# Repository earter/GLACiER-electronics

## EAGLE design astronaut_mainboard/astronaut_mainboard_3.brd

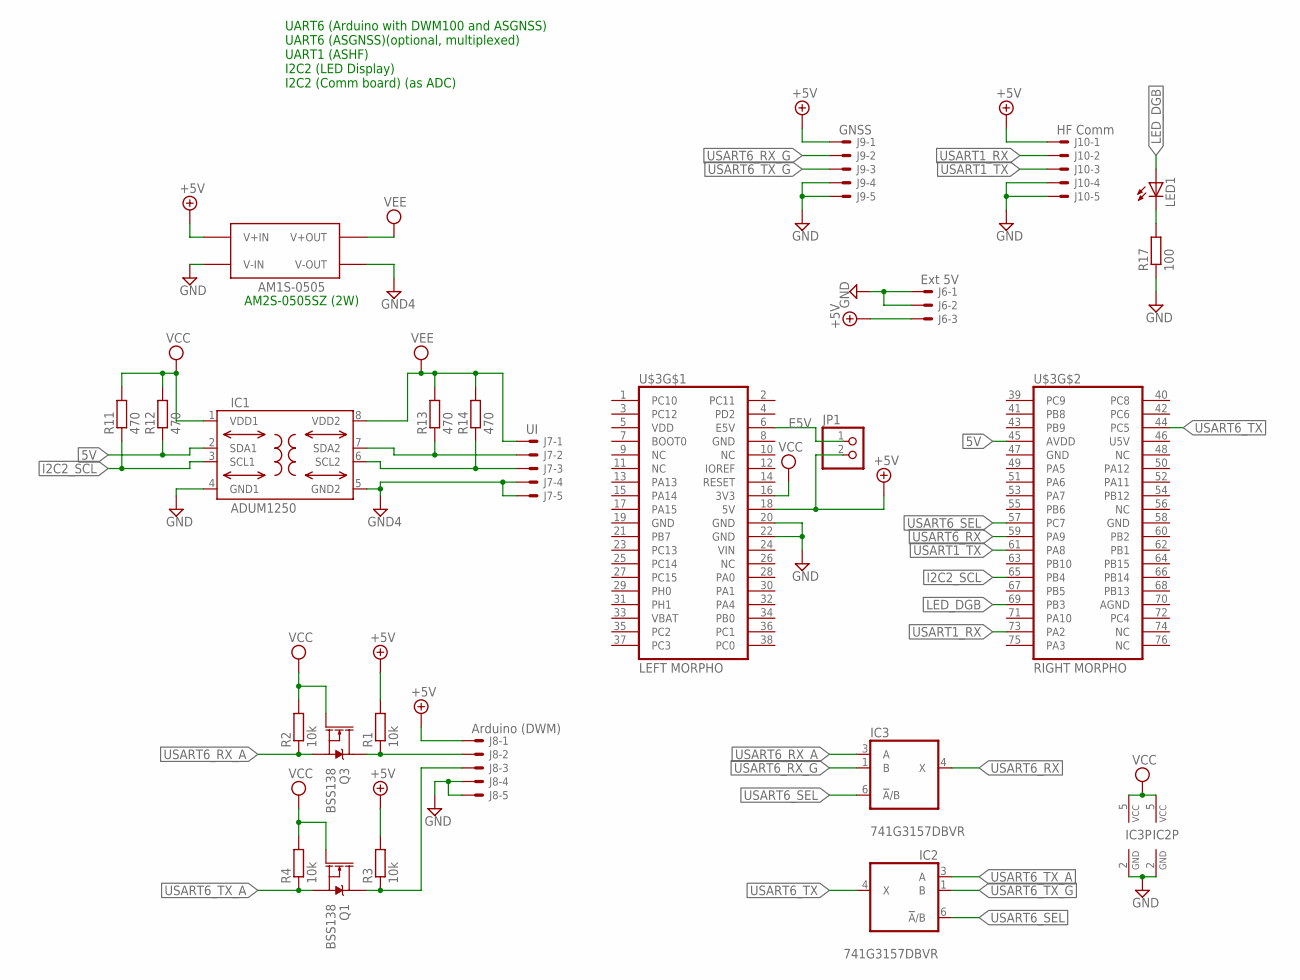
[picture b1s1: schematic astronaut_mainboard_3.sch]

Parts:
IC1: ADUM1250; SO8-COOL
IC2, IC3: 741G3157DBVR; DBV_R-PDSO-G6
J6: Ext 5V; 7395-03
J7: UI; 7395-05
J8: Arduino (DWM); 7395-05
J9: GNSS; 7395-05
J10: HF Comm; 7395-05
JP1: PINHD-1X2; 1X02
LED1: LEDSML1206; SML1206
Q1, Q3: BSS138; SOT23-3
R1, R2, R3, R4: 10k; R0805
R11, R12, R13, R14: 470; R0805
R17: 100; R0805
U$2: AM1S-0505; SIP4
U$3: NUCLEO_F411RE_MORPHO; MORPHO_HEADERS

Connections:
5V: IC1.2 (SDA1), R12.1, U$3.45 (AVDD)
+5V: J6.3, J8.1, J9.1, J10.1, JP1.2, R1.2, R3.2, U$2.P$2 (V+IN), U$3.18 (5V)
AGND: U$3.70 (AGND)
ARDU_RX: J8.2, Q3.3 (D), R1.1
ARDU_TX: J8.3, Q1.3 (D), R3.1
E5V: JP1.1, U$3.6 (E5V)
GND: IC1.4 (GND1), IC2.2 (GND), IC3.2 (GND), J6.1, J6.2, J8.4, J8.5, J9.4, J9.5, J10.4, J10.5, R17.1, U$2.P$1 (V-IN), U$3.8 (GND), U$3.19 (GND), U$3.20 (GND), U$3.22 (GND), U$3.47 (GND), U$3.58 (GND)
GND4: IC1.5 (GND2), J7.4, J7.5, U$2.P$3 (V-OUT)
I2C2_SCL: IC1.3 (SCL1), R11.1, U$3.65 (PB4)
LED_DGB: LED1.A, U$3.69 (PB3)
unnamed: LED1.C, R17.2
U5V: U$3.46 (U5V)
UI_SCL: IC1.6 (SCL2), J7.3, R14.1
UI_SDA: IC1.7 (SDA2), J7.2, R13.1
USART1_RX: J10.2, U$3.73 (PA2)
USART1_TX: J10.3, U$3.61 (PA8)
USART6_RX: IC3.4 (X), U$3.59 (PA9)
USART6_RX_A: IC3.3 (A), Q3.2 (S), R2.1
USART6_RX_G: IC3.1 (B), J9.2
USART6_SEL: IC2.6 (!A!/B), IC3.6 (!A!/B), U$3.57 (PC7)
USART6_TX: IC2.4 (X), U$3.44 (PC5)
USART6_TX_A: IC2.3 (A), Q1.2 (S), R4.1
USART6_TX_G: IC2.1 (B), J9.3
VBAT: U$3.33 (VBAT)
VCC: IC1.1 (VDD1), IC2.5 (VCC), IC3.5 (VCC), Q1.1 (G), Q3.1 (G), R2.2, R4.2, R11.2, R12.2, U$3.16 (3V3)
VDD: U$3.5 (VDD)
VEE: IC1.8 (VDD2), J7.1, R13.2, R14.2, U$2.P$4 (V+OUT)
VIN: U$3.24 (VIN)

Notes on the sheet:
UART6 (Arduino with DWM100 and ASGNSS) UART6 (ASGNSS)(optional, multiplexed) UART1 (ASHF) I2C2 (LED Display) I2C2 (Comm board) (as ADC)
AM2S-0505SZ (2W)

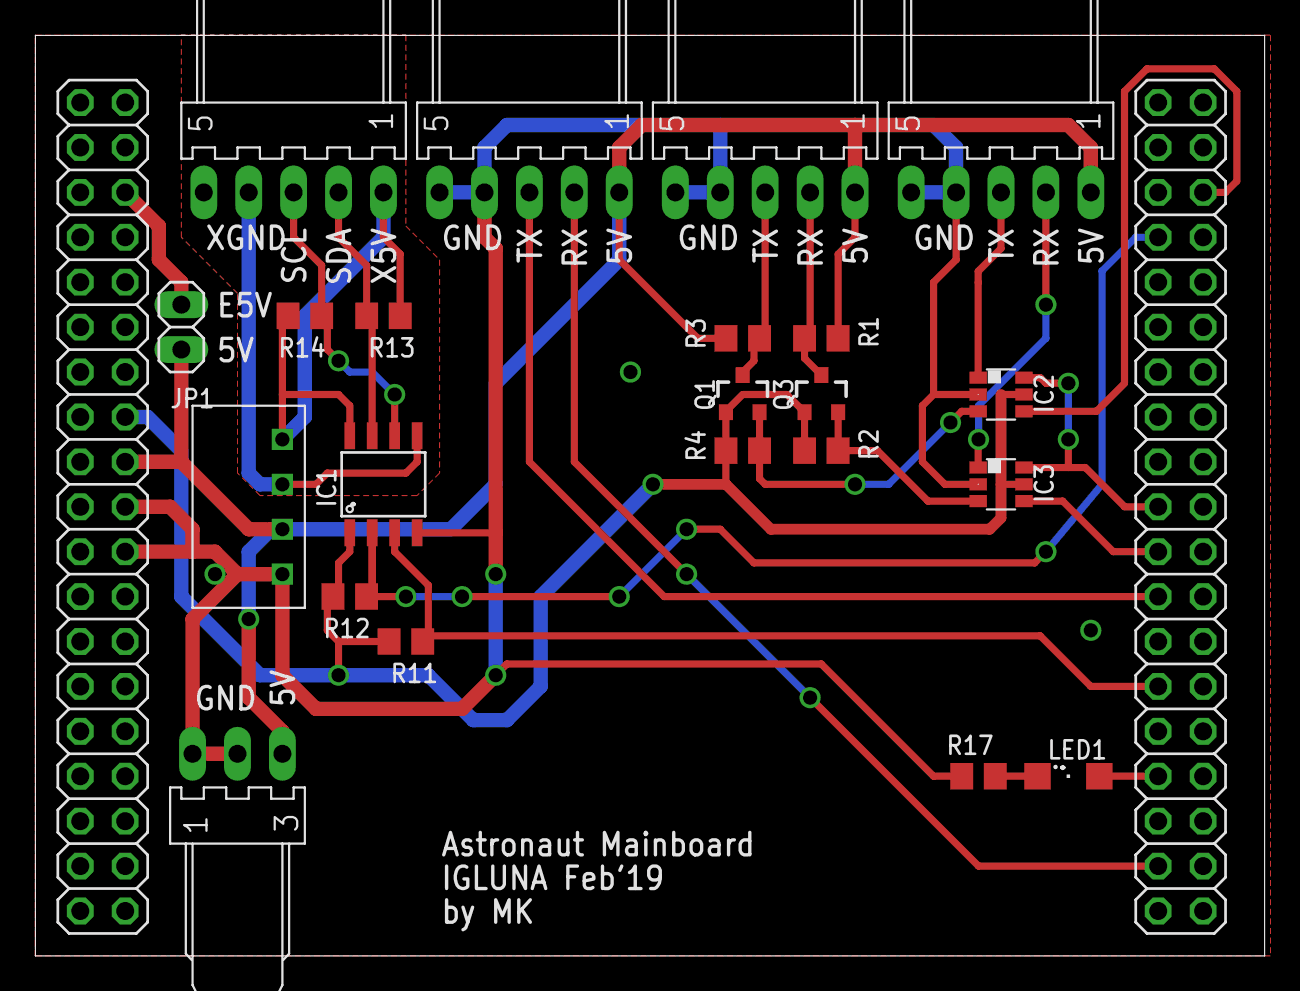
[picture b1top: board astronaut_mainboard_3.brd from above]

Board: 2 copper layers, 69.5 x 52.1 mm, 23 parts (0 on the bottom side), 23 nets.

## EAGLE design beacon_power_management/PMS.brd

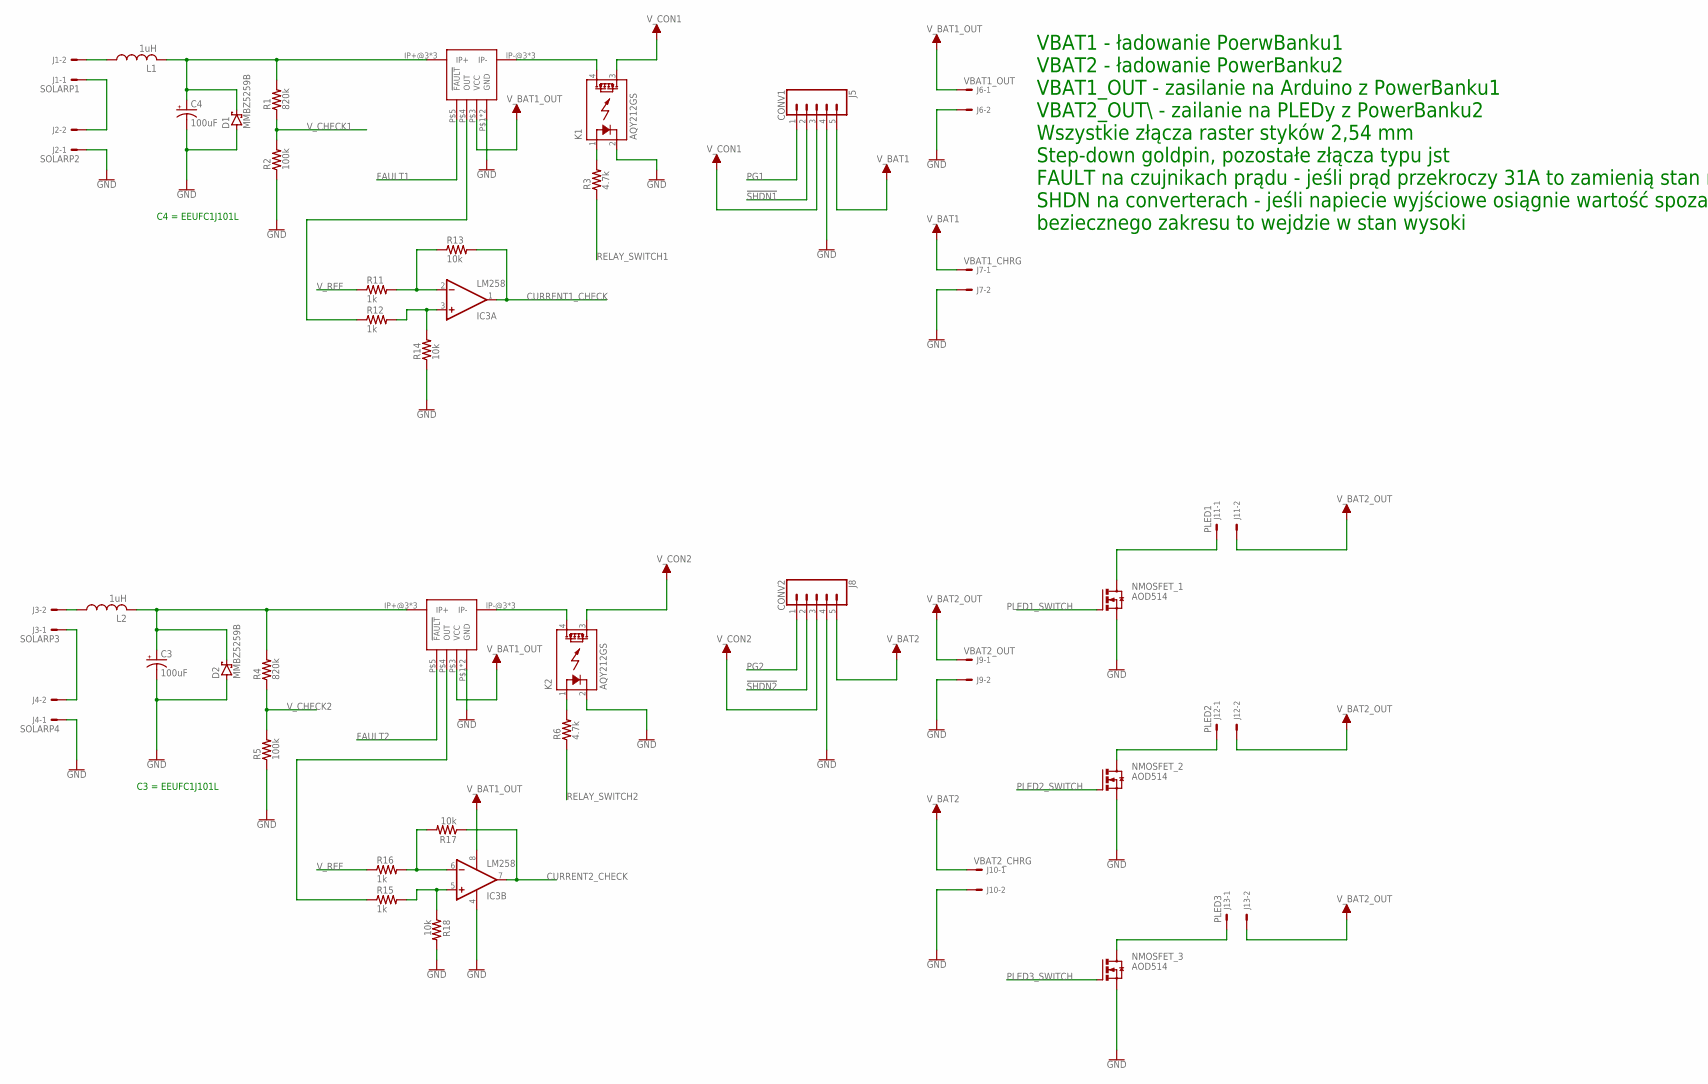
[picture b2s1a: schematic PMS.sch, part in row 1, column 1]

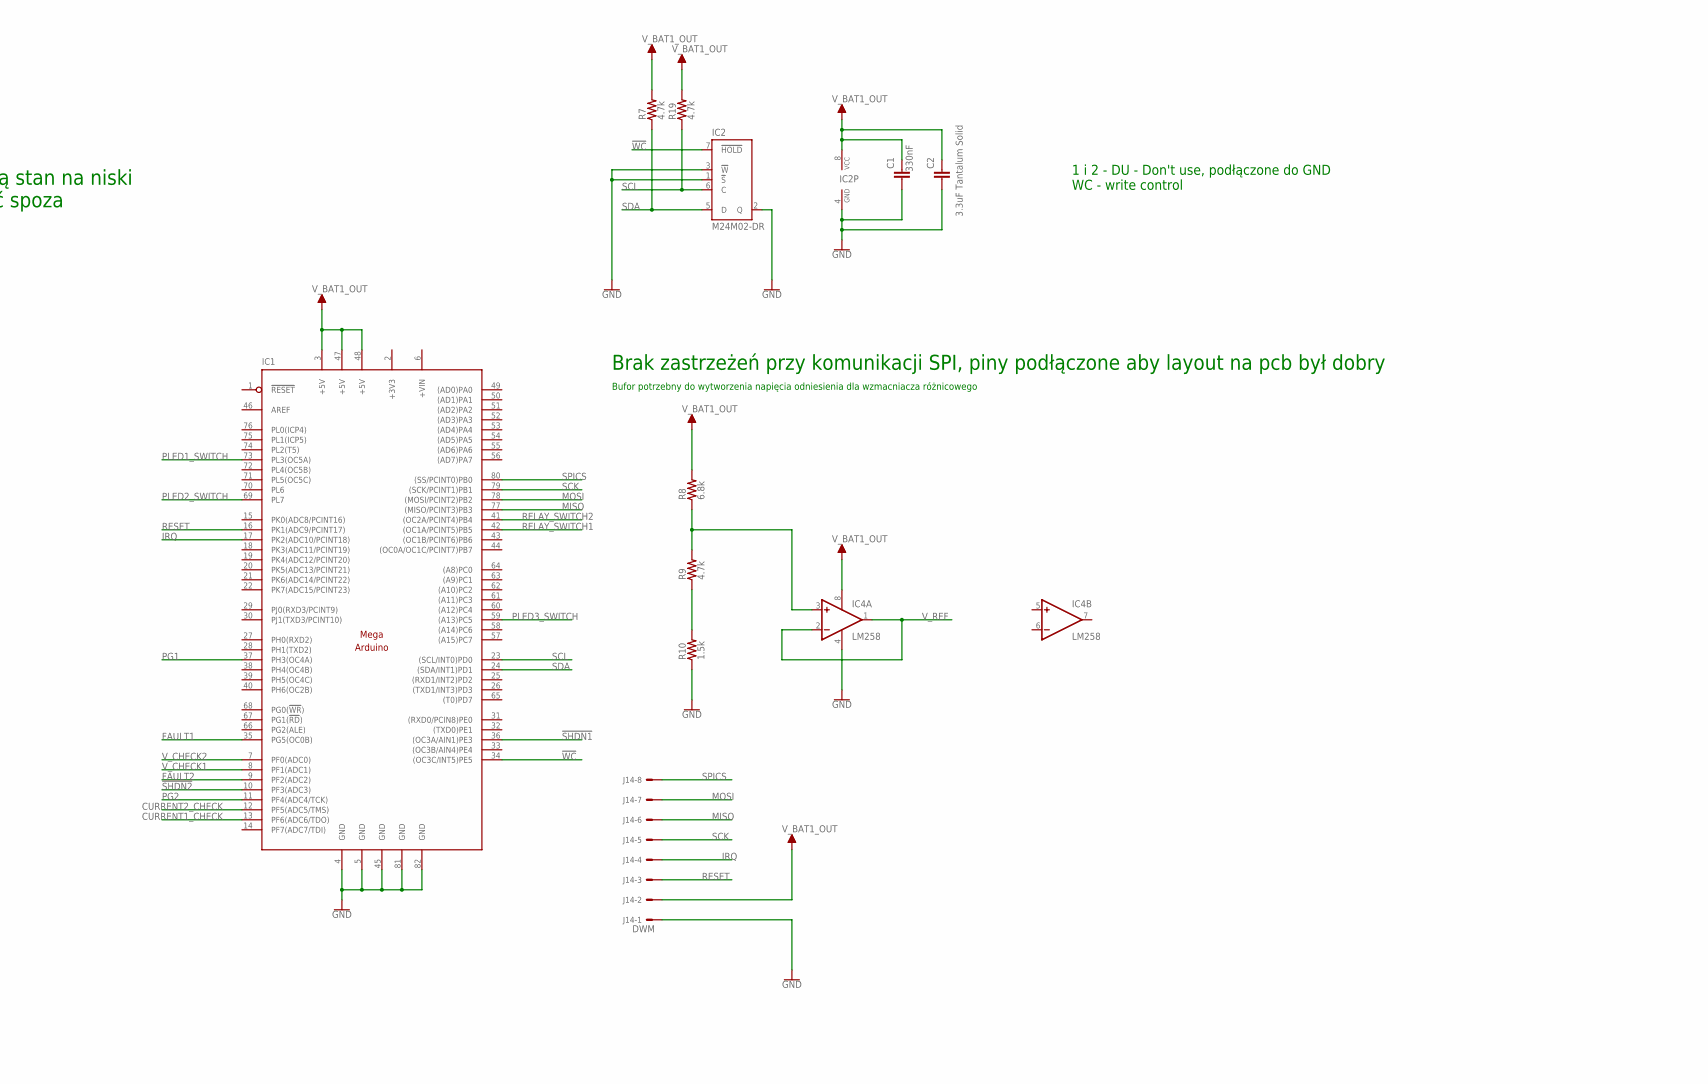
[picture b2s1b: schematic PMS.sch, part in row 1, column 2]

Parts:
C1: 330nF; C0805
C2: 3.3uF Tantalum Solid; C1206
C3, C4: 100uF; E3,5-8
CURRETN_SENS: ACS711EXSH; POLOLU2453_SMALL_HOLES
D1, D2: MMBZ5259B; SOT23
IC1: MEGAARDUINO_13; MEGA_ARDUINO_3
IC2: M24M02-DR; SO08
IC3, IC4: LM258; SO08
J1: SOLARP1; 6410-02
J2: SOLARP2; 6410-02
J3: SOLARP3; 6410-02
J4: SOLARP4; 6410-02
J5: CONV1; 1X05
J6: VBAT1_OUT; 6410-02
J7: VBAT1_CHRG; 6410-02
J8: CONV2; 1X05
J9: VBAT2_OUT; 6410-02
J10: VBAT2_CHRG; 6410-02
J11: PLED1; 6410-02
J12: PLED2; 6410-02
J13: PLED3; 6410-02
J14: DWM; 6410-08
K1, K2: AQY212GS; SOP04
L1, L2: 1uH; L3225M
NMOSFET_1, NMOSFET_2, NMOSFET_3: AOD514; TO252
R1, R4: 820k; R0805
R2, R5: 100k; R0805
R3, R6, R7, R9, R19: 4.7k; R0805
R8: 6.8k; R0805
R10: 1.5k; R0805
R11, R12, R15, R16: 1k; R0805
R13, R14, R17, R18: 10k; R0805
U$2: ACS711EXSH; POLOLU2453_SMALL_HOLES

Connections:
!SHDN1: IC1.36 ((OC3A/AIN1)PE3), J5.2
!SHDN2: IC1.10 (PF3(ADC3)), J8.2
!WC: IC1.34 ((OC3C/INT5)PE5), IC2.7 (!HOLD)
+3V3: IC1.2 (+3V3)
+VIN: IC1.6 (+VIN)
CURRENT1_CHECK: IC1.13 (PF6(ADC6/TDO)), IC3.1 (OUT), R13.2
CURRENT2_CHECK: IC1.12 (PF5(ADC5/TMS)), IC3.7 (OUT), R17.1
FAULT1: CURRETN_SENS.P$5 (!FAULT), IC1.35 (PG5(OC0B))
FAULT2: IC1.9 (PF2(ADC2)), U$2.P$5 (!FAULT)
GND: C1.1, C2.1, C3.-, C4.-, CURRETN_SENS.P$1 (GND), CURRETN_SENS.P$2 (GND), D1.1 (A), D2.1 (A), IC1.4 (GND), IC1.5 (GND), IC1.45 (GND), IC1.81 (GND), IC1.82 (GND), IC2.1 (!S), IC2.2 (Q), IC2.3 (!W), IC2.4 (GND), IC3.4 (V-), IC4.4 (V-), J2.1, J4.1, J5.4, J6.2, J7.2, J8.4, J9.2, J10.2, J14.1, K1.2 (K), K2.2 (K), NMOSFET_1.3 (S), NMOSFET_2.3 (S), NMOSFET_3.3 (S), R2.1, R5.1, R10.1, R14.1, R18.2, U$2.P$1 (GND), U$2.P$2 (GND)
IRQ: IC1.17 (PK2(ADC10/PCINT18)), J14.4
MISO: IC1.77 ((MISO/PCINT3)PB3), J14.6
MOSI: IC1.78 ((MOSI/PCINT2)PB2), J14.7
unnamed: K1.1 (A), R3.2
unnamed: CURRETN_SENS.IP-@3 (IP-), CURRETN_SENS.IP-@4 (IP-), CURRETN_SENS.IP-@5 (IP-), K1.4 (DS1)
unnamed: J3.1, J4.2
unnamed: J12.1, NMOSFET_2.4 (D)
unnamed: K2.1 (A), R6.2
unnamed: J13.1, NMOSFET_3.4 (D)
unnamed: IC3.2 (-IN), R11.2, R13.1
unnamed: J11.1, NMOSFET_1.4 (D)
unnamed: J1.1, J2.2
unnamed: K2.4 (DS1), U$2.IP-@3 (IP-), U$2.IP-@4 (IP-), U$2.IP-@5 (IP-)
unnamed: IC4.3 (+IN), R8.1, R9.2
unnamed: CURRETN_SENS.P$4 (OUT), R12.1
unnamed: IC3.6 (-IN), R16.2, R17.2
unnamed: IC3.5 (+IN), R15.2, R18.1
unnamed: IC3.3 (+IN), R12.2, R14.2
unnamed: R15.1, U$2.P$4 (OUT)
unnamed: R9.1, R10.2
unnamed: C3.+, D2.3 (C), L2.2, R4.2, U$2.IP+@3 (IP+), U$2.IP+@4 (IP+), U$2.IP+@5 (IP+)
unnamed: C4.+, CURRETN_SENS.IP+@3 (IP+), CURRETN_SENS.IP+@4 (IP+), CURRETN_SENS.IP+@5 (IP+), D1.3 (C), L1.2, R1.2
unnamed: J1.2, L1.1
unnamed: J3.2, L2.1
PG1: IC1.37 (PH3(OC4A)), J5.1
PG2: IC1.11 (PF4(ADC4/TCK)), J8.1
PLED1_SWITCH: IC1.73 (PL3(OC5A)), NMOSFET_1.1 (G)
PLED2_SWITCH: IC1.69 (PL7), NMOSFET_2.1 (G)
PLED3_SWITCH: IC1.59 ((A13)PC5), NMOSFET_3.1 (G)
RELAY_SWITCH1: IC1.42 ((OC1A/PCINT5)PB5), R3.1
RELAY_SWITCH2: IC1.41 ((OC2A/PCINT4)PB4), R6.1
RESET: IC1.16 (PK1(ADC9/PCINT17)), J14.3
SCK: IC1.79 ((SCK/PCINT1)PB1), J14.5
SCL: IC1.23 ((SCL/INT0)PD0), IC2.6 (C), R19.1
SDA: IC1.24 ((SDA/INT1)PD1), IC2.5 (D), R7.1
SPICS: IC1.80 ((SS/PCINT0)PB0), J14.8
V2: J5.3, K1.3 (DS2)
V4: J8.3, K2.3 (DS2)
V_BAT1: J5.5, J7.1
V_BAT1_OUT: C1.2, C2.2, CURRETN_SENS.P$3 (VCC), IC1.3 (+5V), IC1.47 (+5V), IC1.48 (+5V), IC2.8 (VCC), IC3.8 (V+), IC4.8 (V+), J6.1, J14.2, R7.2, R8.2, R19.2, U$2.P$3 (VCC)
V_BAT2: J8.5, J10.1
V_BAT4: J9.1, J11.2, J12.2, J13.2
V_CHECK1: IC1.8 (PF1(ADC1)), R1.1, R2.2
V_CHECK2: IC1.7 (PF0(ADC0)), R4.1, R5.2
V_REF: IC4.1 (OUT), IC4.2 (-IN), R11.1, R16.1

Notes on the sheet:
VBAT1 - ładowanie PoerwBanku1 VBAT2 - ładowanie PowerBanku2 VBAT1_OUT - zasilanie na Arduino z PowerBanku1 VBAT2_OUT\ - zailanie na PLEDy z PowerBanku2 Wszystkie złącza raster styków 2,54 mm Step-down goldpin, pozostałe złącza typu jst FAULT na czujnikach prądu - jeśli prąd przekroczy 31A to zamien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
Brak zastrzeżeń przy komunikacji SPI, piny podłączone aby layout na pcb był dobry
1 i 2 - DU - Don't use, podłączone do GND WC - write control
Bufor potrzebny do wytworzenia napięcia odniesienia dla wzmacniacza różnicowego
C4 = EEUFC1J101L
C3 = EEUFC1J101L

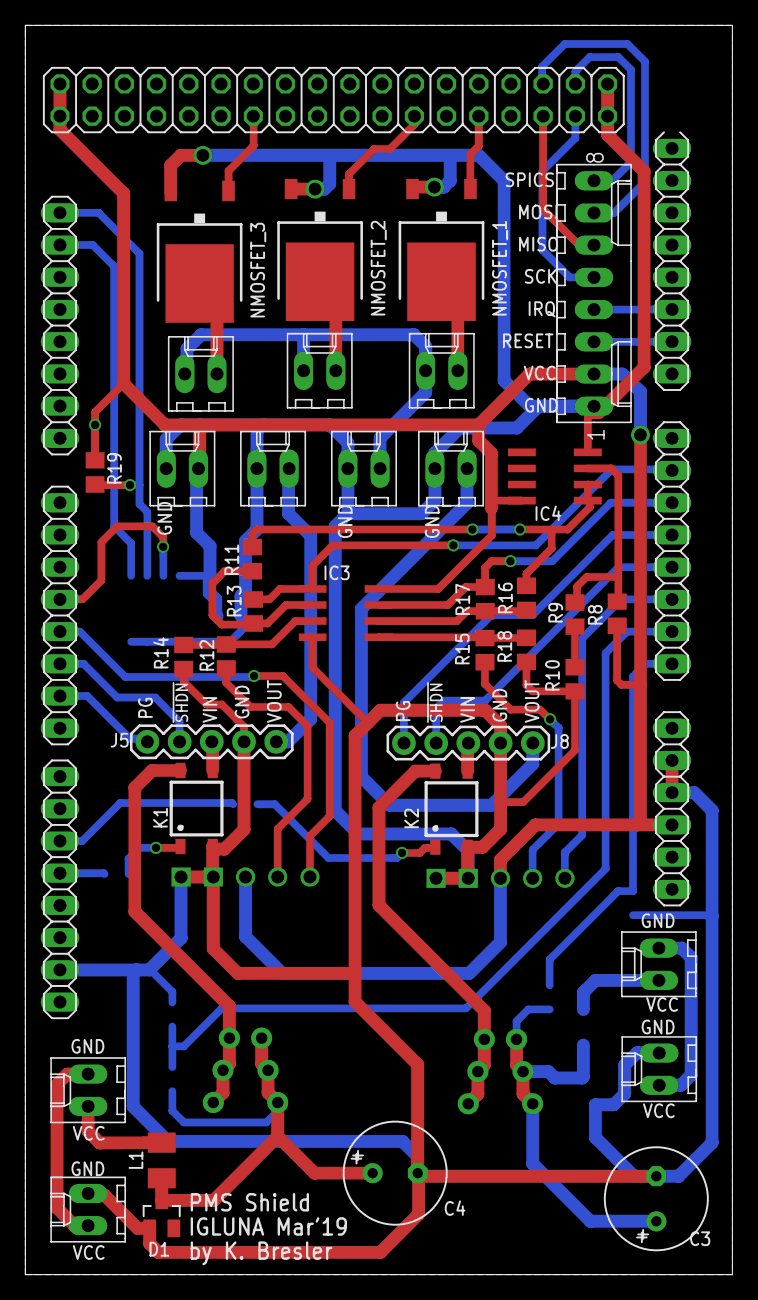
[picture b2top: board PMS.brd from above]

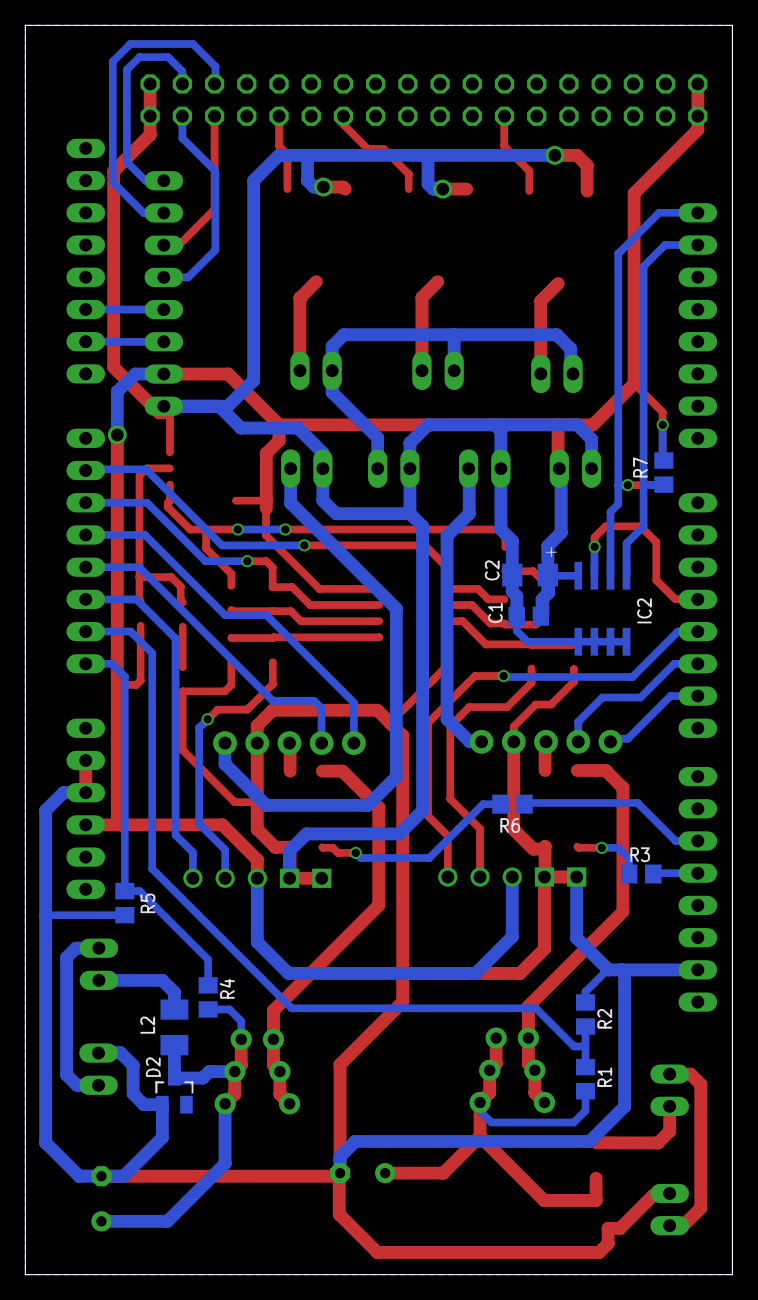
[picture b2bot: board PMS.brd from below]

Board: 2 copper layers, 55.8 x 98.5 mm, 52 parts (12 on the bottom side), 53 nets.

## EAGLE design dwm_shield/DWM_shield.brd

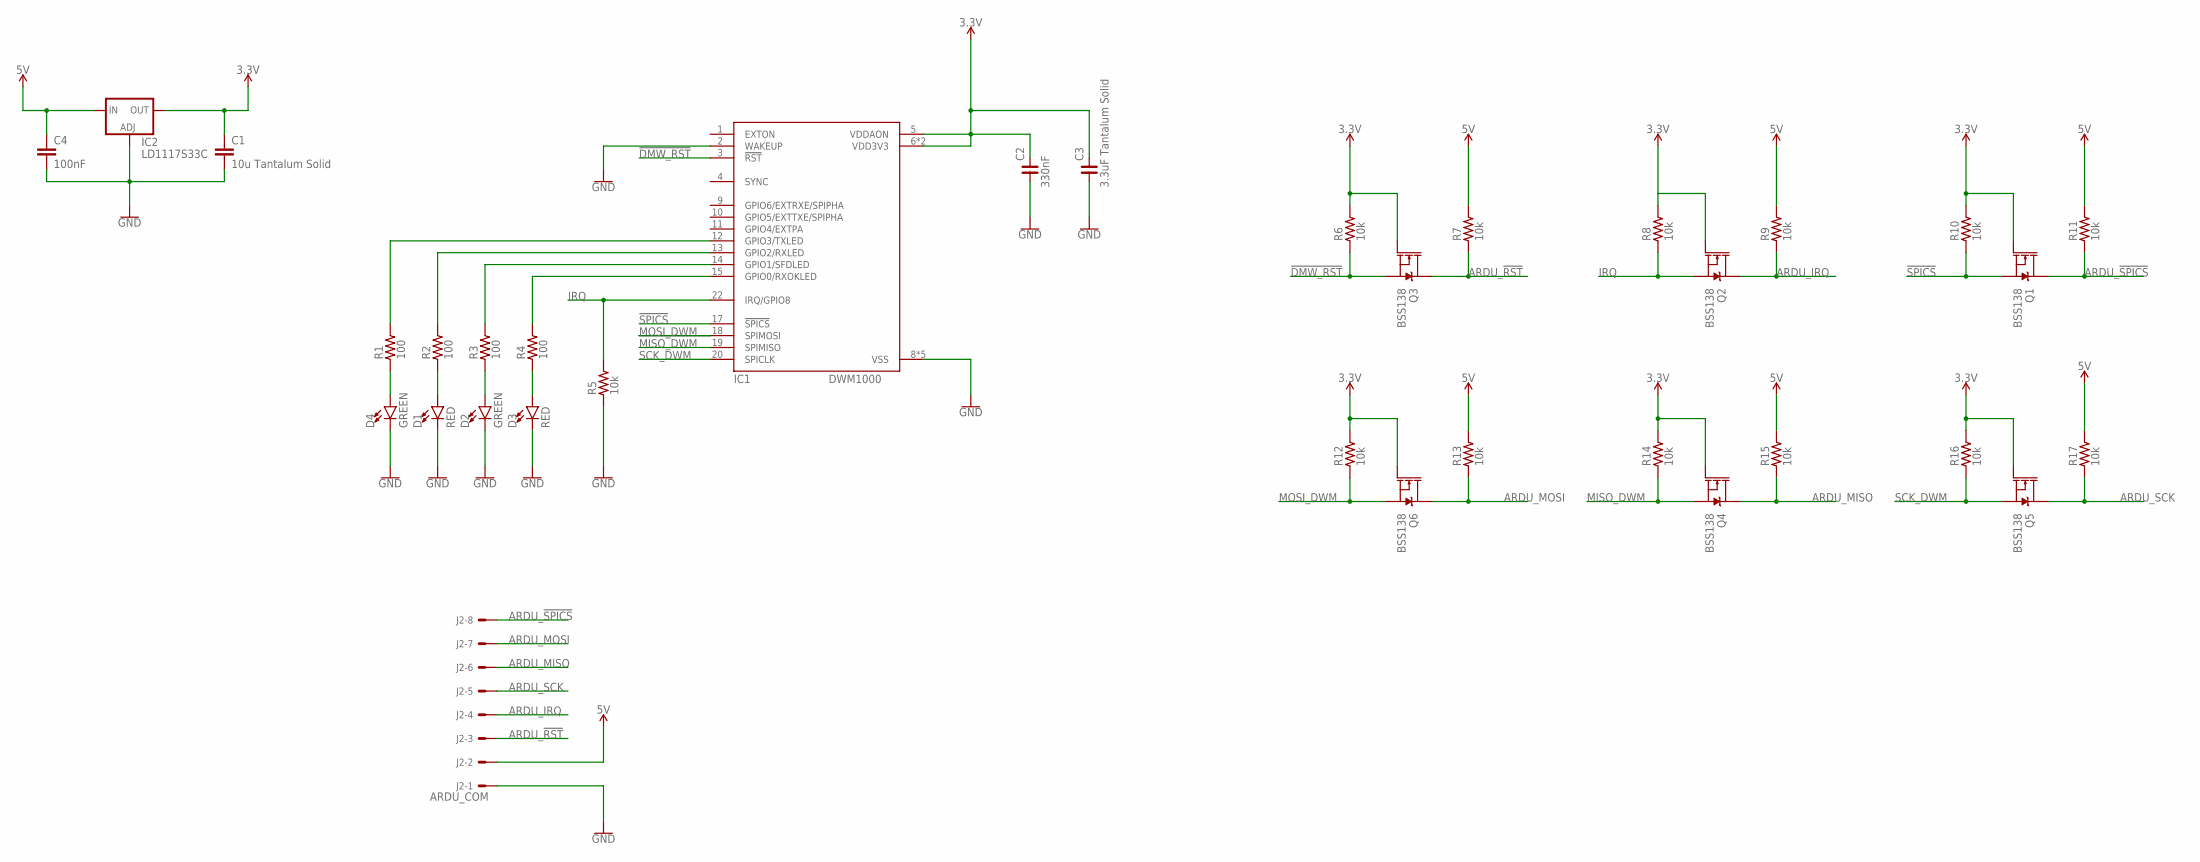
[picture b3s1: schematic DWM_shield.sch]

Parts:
C1: 10u Tantalum Solid; C1206
C2: 330nF; C0805
C3: 3.3uF Tantalum Solid; C1206
C4: 100nF; C0805
D1, D3: RED; LED-1206
D2, D4: GREEN; LED-1206
IC1: DWM1000
IC2: LD1117S33C; SOT223
J2: ARDU_COM; 7395-08
Q1, Q2, Q3, Q4, Q5, Q6: BSS138; SOT23-3
R1, R2, R3, R4: 100; R0805
R5, R6, R7, R8, R9, R10, R11, R12, R13, R14, R15, R16, R17: 10k; R0805

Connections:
3.3V: C1.1, C2.2, C3.2, IC1.5 (VDDAON), IC1.6 (VDD3V3), IC1.7 (VDD3V3), IC2.4 (OUT), Q1.1 (G), Q2.1 (G), Q3.1 (G), Q4.1 (G), Q5.1 (G), Q6.1 (G), R6.2, R8.2, R10.2, R12.2, R14.2, R16.2
5V: C4.1, IC2.3 (IN), J2.2, R7.2, R9.2, R11.2, R13.2, R15.2, R17.2
!DMW_RST: IC1.3 (!RST), Q3.2 (S), R6.1
!SPICS: IC1.17 (!SPICS), Q1.2 (S), R10.1
ARDU_!RST: J2.3, Q3.3 (D), R7.1
ARDU_!SPICS: J2.8, Q1.3 (D), R11.1
ARDU_IRQ: J2.4, Q2.3 (D), R9.1
ARDU_MISO: J2.6, Q4.3 (D), R15.1
ARDU_MOSI: J2.7, Q6.3 (D), R13.1
ARDU_SCK: J2.5, Q5.3 (D), R17.1
GND: C1.2, C2.1, C3.1, C4.2, D1.C, D2.C, D3.C, D4.C, IC1.2 (WAKEUP), IC1.8 (VSS), IC1.16 (VSS), IC1.21 (VSS), IC1.23 (VSS), IC1.24 (VSS), IC2.1 (ADJ), J2.1, R5.1
IRQ: IC1.22 (IRQ/GPIO8), Q2.2 (S), R5.2, R8.1
MISO_DWM: IC1.19 (SPIMISO), Q4.2 (S), R14.1
MOSI_DWM: IC1.18 (SPIMOSI), Q6.2 (S), R12.1
unnamed: IC1.15 (GPIO0/RXOKLED), R4.2
unnamed: IC1.14 (GPIO1/SFDLED), R3.2
unnamed: D4.A, R1.1
unnamed: IC1.13 (GPIO2/RXLED), R2.2
unnamed: IC1.12 (GPIO3/TXLED), R1.2
unnamed: D2.A, R3.1
unnamed: D1.A, R2.1
unnamed: D3.A, R4.1
SCK_DWM: IC1.20 (SPICLK), Q5.2 (S), R16.1

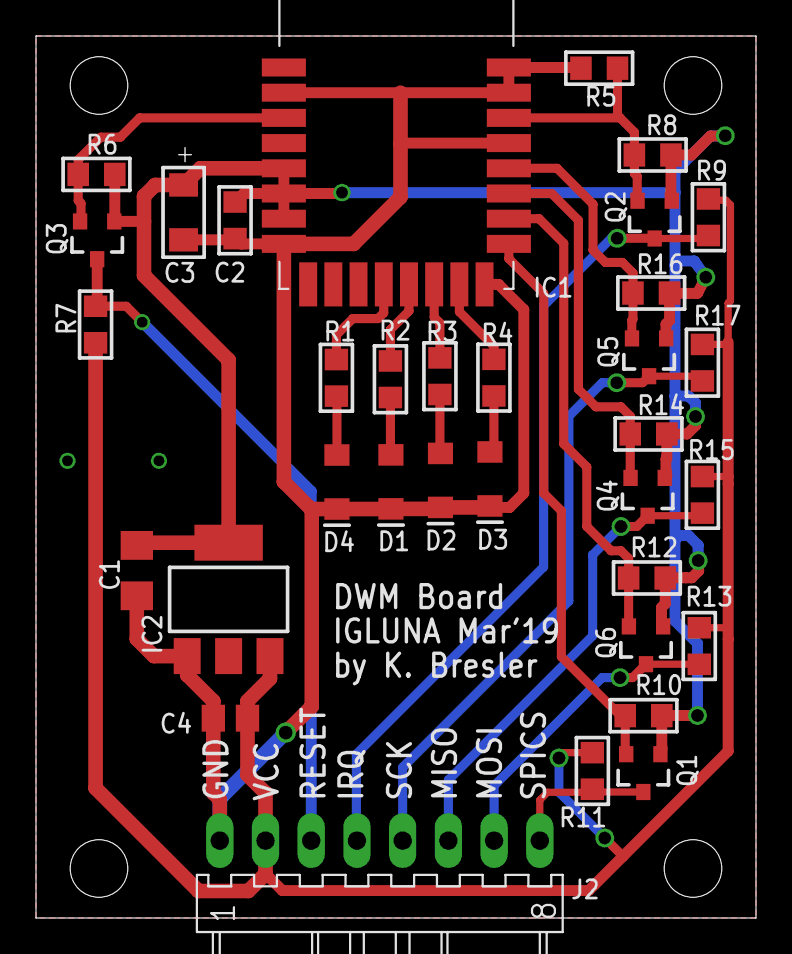
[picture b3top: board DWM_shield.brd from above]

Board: 2 copper layers, 40.0 x 49.0 mm, 34 parts (0 on the bottom side), 23 nets.

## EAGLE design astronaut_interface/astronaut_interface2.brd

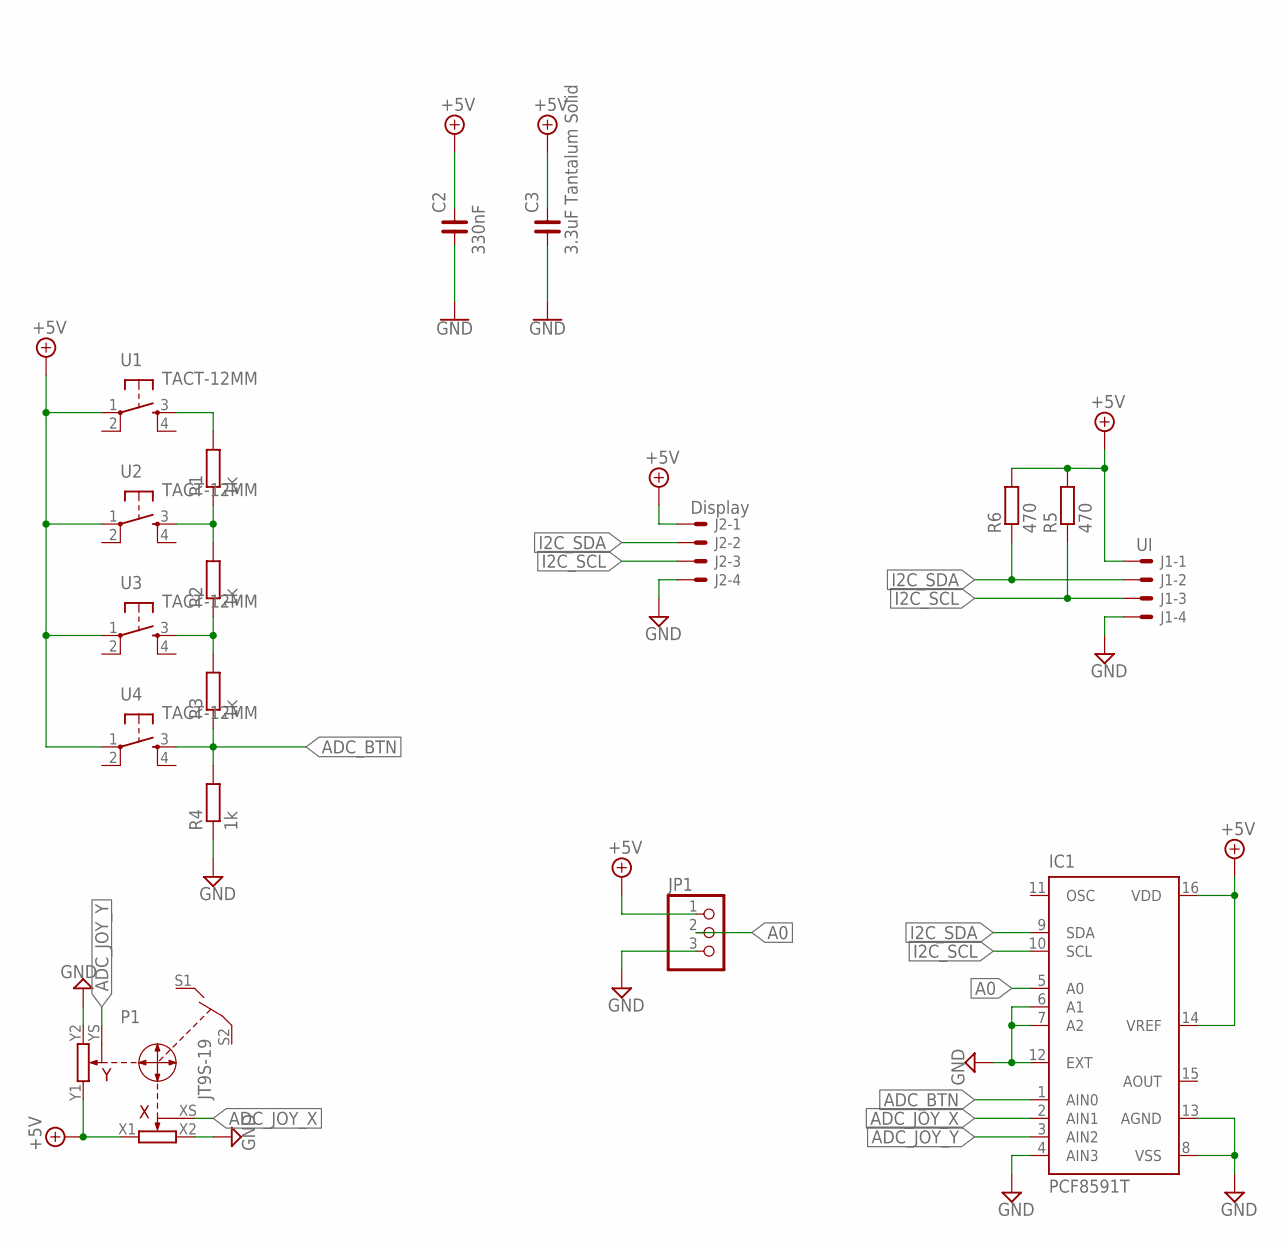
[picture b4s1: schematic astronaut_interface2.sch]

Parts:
C2: 330nF; C0805
C3: 3.3uF Tantalum Solid; C1206
IC1: PCF8591T; SO16W
J1: UI; 7395-04
J2: Display; 7395-04
JP1: PINHD-1X3; 1X03
P1: JT9S-19; JT9S-1P
R1, R2, R3, R4: 1k; R0805
R5, R6: 470; M0805
U1, U2, U3, U4: TACT-12MM; TACT-12_THT

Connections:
+5V: C2.2, C3.2, IC1.14 (VREF), IC1.16 (VDD), J1.1, J2.1, JP1.1, P1.X1, P1.Y1, R5.2, R6.2, U1.1, U2.1, U3.1, U4.1
A0: IC1.5 (A0), JP1.2
ADC_BTN: IC1.1 (AIN0), R3.1, R4.2, U4.3
ADC_JOY_X: IC1.2 (AIN1), P1.XS
ADC_JOY_Y: IC1.3 (AIN2), P1.YS
GND: C2.1, C3.1, IC1.4 (AIN3), IC1.6 (A1), IC1.7 (A2), IC1.8 (VSS), IC1.12 (EXT), IC1.13 (AGND), J1.4, J2.4, JP1.3, P1.X2, P1.Y2, R4.1
I2C_SCL: IC1.10 (SCL), J1.3, J2.3, R5.1
I2C_SDA: IC1.9 (SDA), J1.2, J2.2, R6.1
unnamed: R1.2, U1.3
unnamed: R2.1, R3.2, U3.3
unnamed: R1.1, R2.2, U2.3

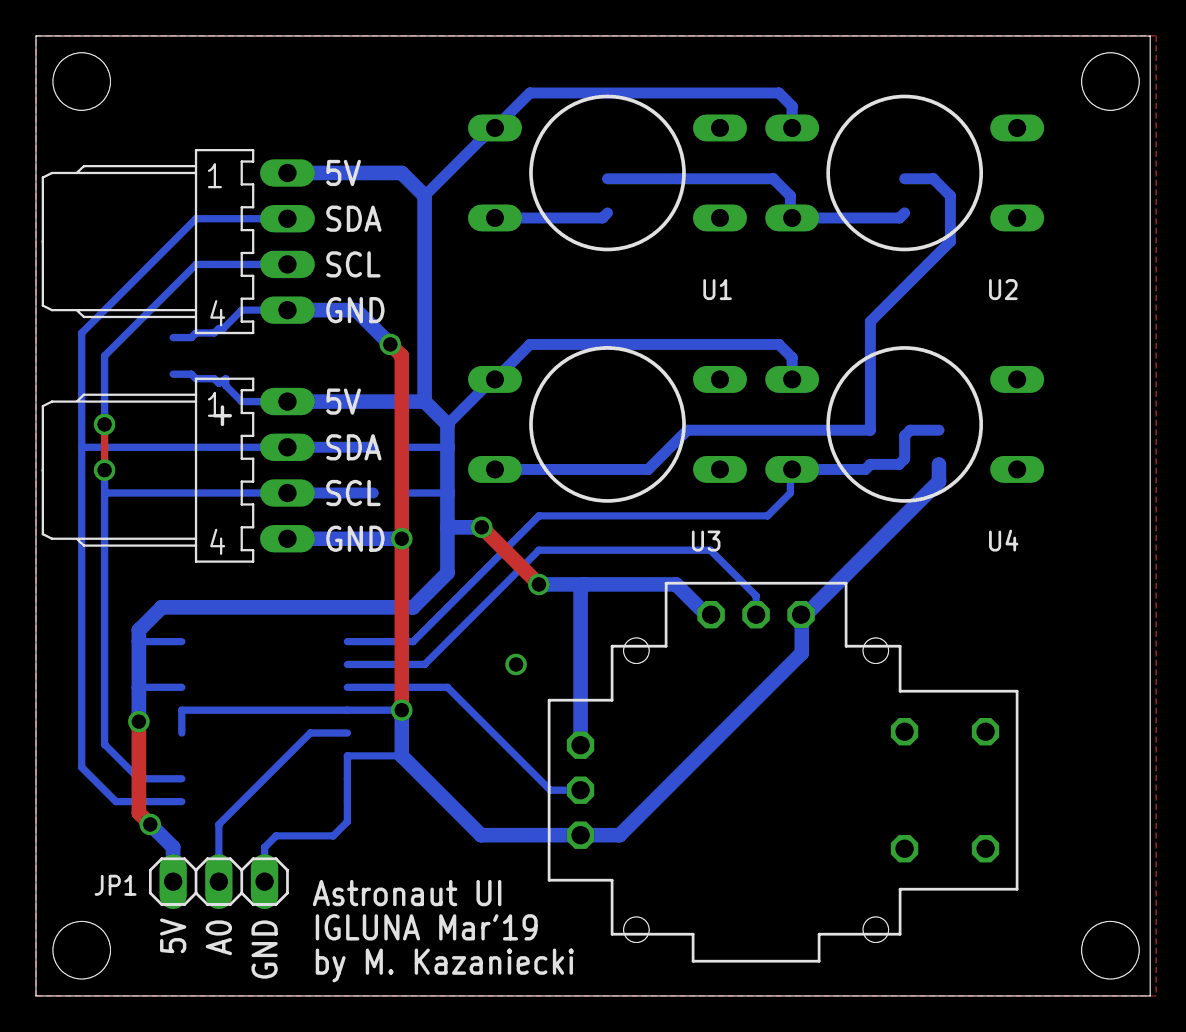
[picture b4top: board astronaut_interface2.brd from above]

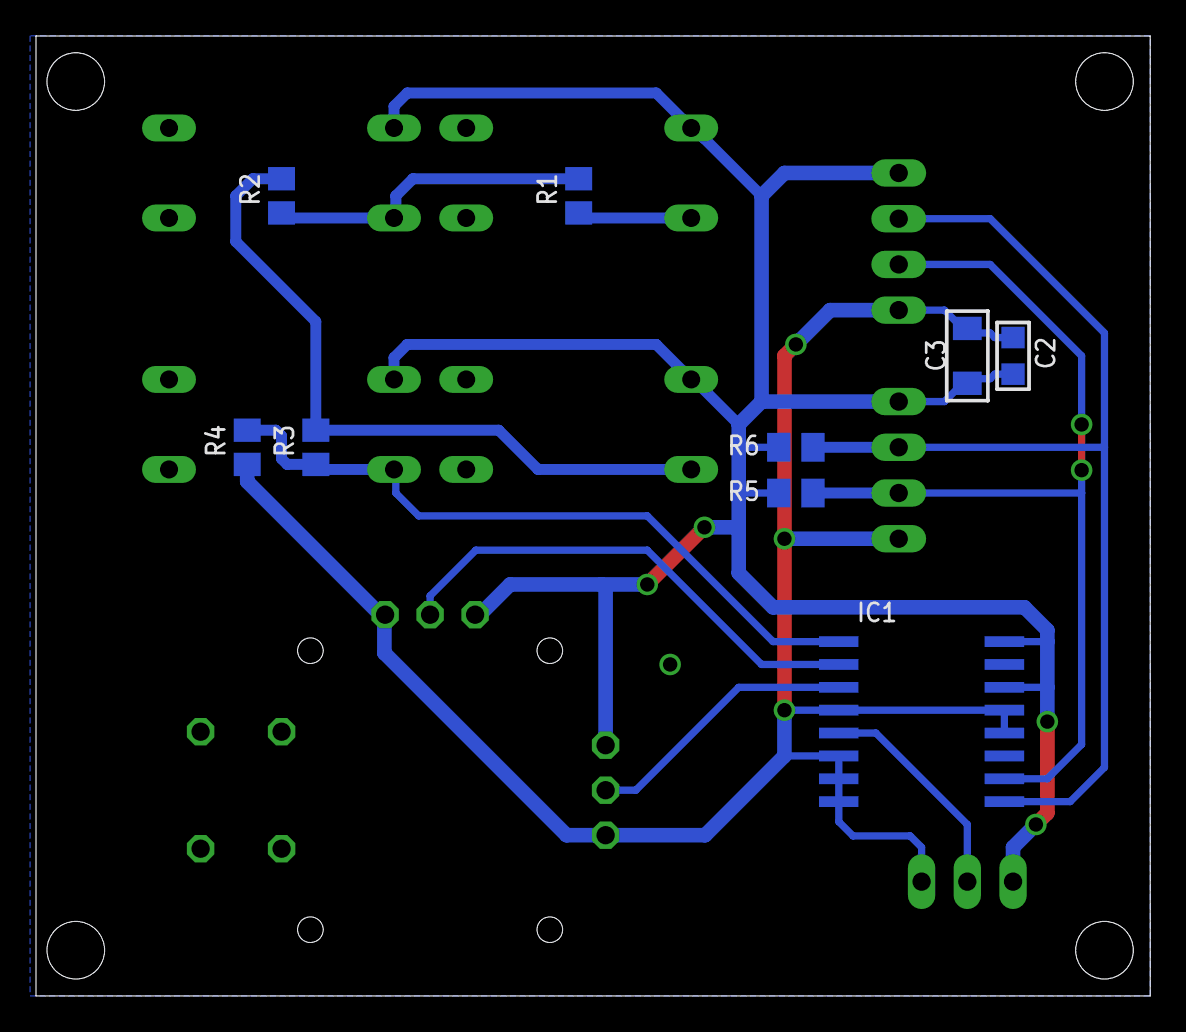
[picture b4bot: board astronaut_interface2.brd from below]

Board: 2 copper layers, 61.9 x 53.3 mm, 17 parts (9 on the bottom side), 11 nets.

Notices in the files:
parts and their libraries:
SparkFun-PowerSymbols: Licensing: Creative Commons ShareAlike 4.0 International - https://creativecommons.org/licenses/by-sa/4.0
rc-master-smd: Copyright (C) 2007, Bob Starr
